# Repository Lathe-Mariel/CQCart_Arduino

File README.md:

# CQCart_Arduino
CQCart Arduino

# Overview
CQ出版から発売されているインバータ・キット2に搭載されているNUCLEOボードを，Arduino Uno R4に換装するための変換基板データを置いてあります．  
KiCADのプロジェクトになっているので，独自に改造して使用することもできます．  
This PCB board was made as a conversion board for Inverter Kit2 that is selling by CQ pub. Using this board, you can attach Arduino Uno R4 as an alternative to NUCLEO.  
 There's Garber data made by KiCAD.

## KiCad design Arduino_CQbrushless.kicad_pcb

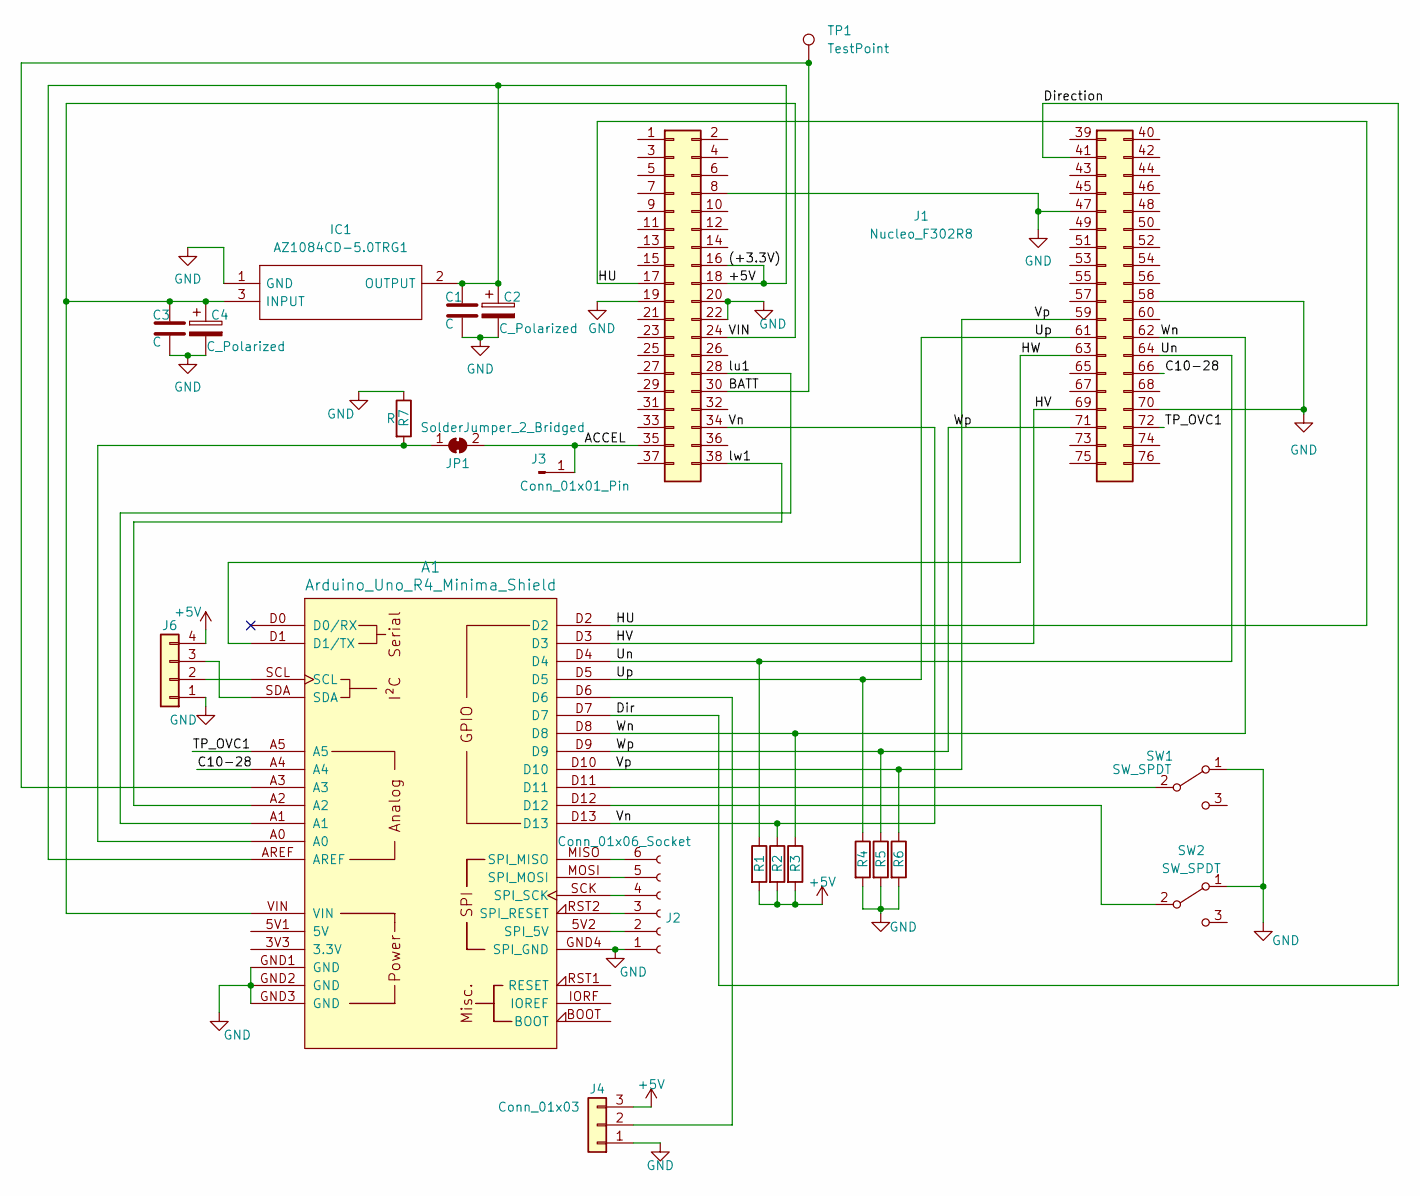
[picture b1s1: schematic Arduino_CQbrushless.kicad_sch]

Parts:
A1: Arduino_Uno_R4_Minima_Shield
C1: C; C_0805_2012Metric_Pad1.18x1.45mm_HandSolder
C2, C4: C_Polarized; CP_Radial_D8.0mm_P3.50mm
C3: C; C_0603_1608Metric_Pad1.08x0.95mm_HandSolder
IC1: AZ1084CD-5.0TRG1; AZ1084CD50TRG1; Manufacturer_Part_Number AZ1084CD-5.0TRG1
J1: Nucleo_F302R8; Nucleo
J2: Conn_01x06_Socket; PinHeader_1x06_P2.54mm_Vertical
J3: Conn_01x01_Pin; PinHeader_1x01_P2.54mm_Vertical
J4: Conn_01x03; PinSocket_1x03_P2.54mm_Vertical
J6: Conn_01x04; PinHeader_1x04_P2.54mm_Vertical
JP1: SolderJumper_2_Bridged; SolderJumper-2_P1.3mm_Bridged_Pad1.0x1.5mm
R1, R2, R3, R4, R5, R6: R; R_Axial_DIN0309_L9.0mm_D3.2mm_P12.70mm_Horizontal
R7: R; R_0603_1608Metric_Pad0.98x0.95mm_HandSolder
SW1, SW2: SW_SPDT; PinHeader_1x03_P2.54mm_Vertical
TP1: TestPoint; TestPoint_Pad_D1.5mm

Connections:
+5V: A1.AREF, C1.1, C2.1, IC1.2 (OUTPUT), J1.16, J1.18, J4.3, J6.4, R1.2, R2.2, R3.2
/ACCEL: J1.35, J3.1, JP1.2 (B)
/BATT: A1.A3, J1.30, TP1.1
/C10-28: A1.A4, J1.66
/Dir: A1.D7, J1.41
/HU: A1.D2, J1.17
/HV: A1.D3, J1.69
/HW: A1.D1 (D1/TX), J1.63
/TP_OVC1: A1.A5, J1.72
/Un: A1.D4, J1.64, R1.1
/Up: A1.D5, J1.61, R4.1
/VIN: A1.VIN, C3.1, C4.1, IC1.3 (INPUT), J1.24
/Vn: A1.D13, J1.34, R2.1
/Vp: A1.D10, J1.59, R6.1
/Wn: A1.D8, J1.62, R3.1
/Wp: A1.D9, J1.71, R5.1
/lu1: A1.A1, J1.28
/lw1: A1.A2, J1.38
GND: A1.GND1 (GND), A1.GND2 (GND), A1.GND3 (GND), A1.GND4 (SPI_GND), C1.2, C2.2, C3.2, C4.2, IC1.1 (GND), J1.8, J1.19, J1.20, J1.22, J1.47, J1.58, J1.70, J2.1, J4.1, J6.1, R4.2, R5.2, R6.2, R7.1, SW1.1 (A), SW2.1 (A)
unnamed: A1.5V2 (SPI_5V), J2.2
unnamed: A1.MISO (SPI_MISO), J2.6
unnamed: A1.MOSI (SPI_MOSI), J2.5
unnamed: A1.RST2 (SPI_RESET), J2.3
unnamed: A1.SCK (SPI_SCK), J2.4
unnamed: A1.D6, J4.2
unnamed: A1.SCL, J6.2
unnamed: A1.SDA, J6.3
unnamed: A1.A0, JP1.1 (A), R7.2
unnamed: A1.D11, SW1.2 (B)
unnamed: A1.D12, SW2.2 (B)

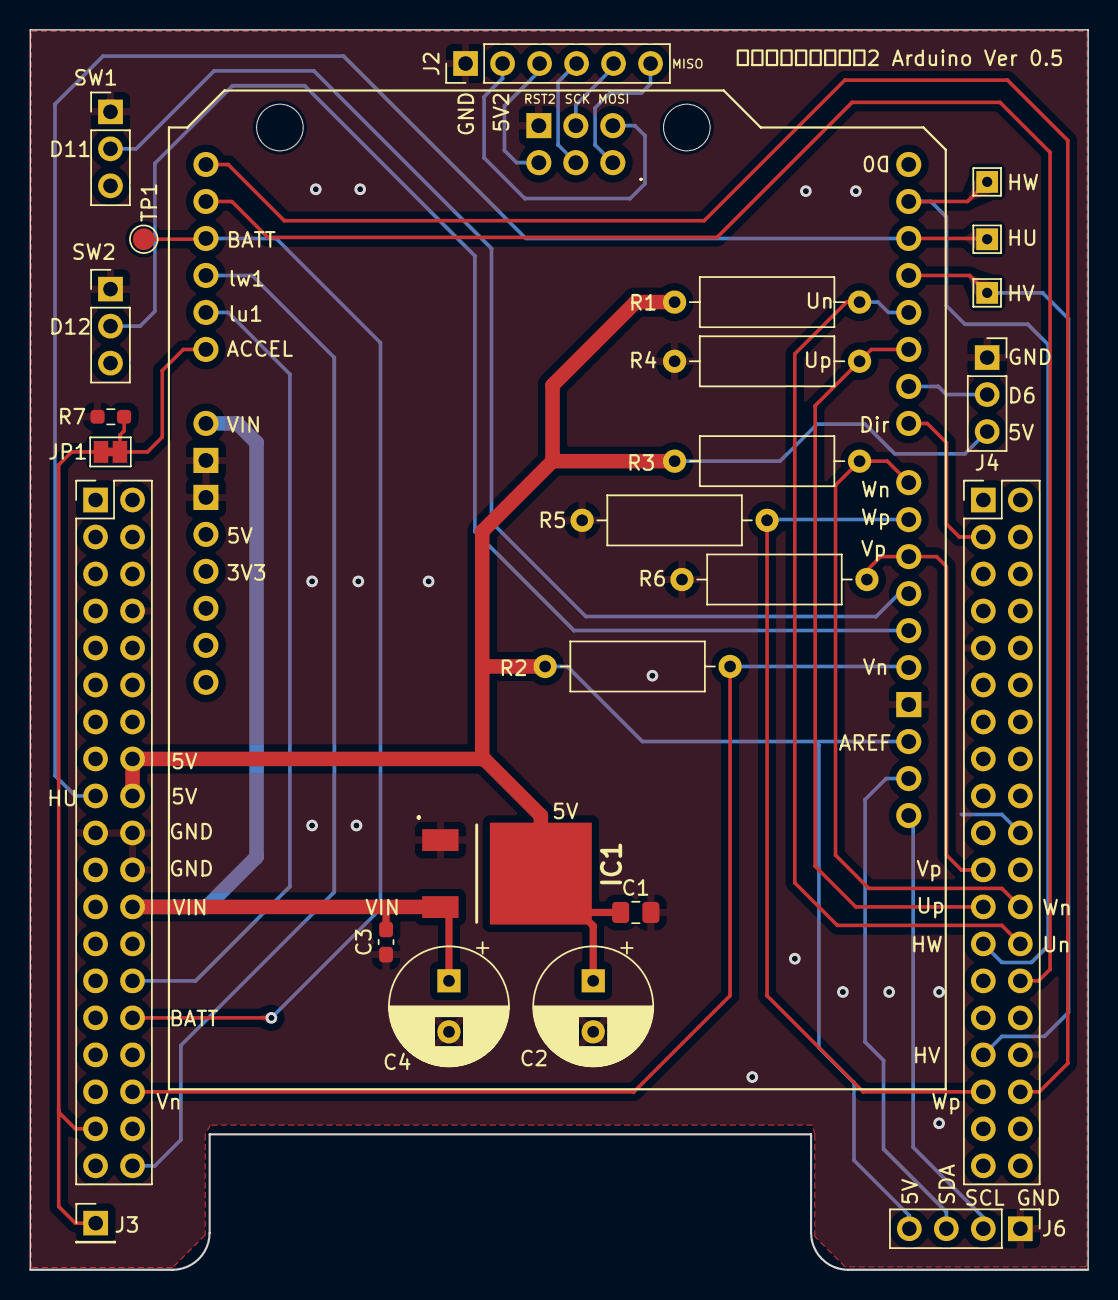
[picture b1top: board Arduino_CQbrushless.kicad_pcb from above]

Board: 2 copper layers, 72.6 x 85.1 mm, 22 parts (1 on the bottom side), 30 nets.

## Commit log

2023-12-28 1228
2024-01-08 0108
2024-01-09 0109
2024-01-18 0118
2024-01-22 0122
2024-02-07 ver0.3
2024-02-09 0209
2024-02-13 ver 0.4 (add LDO)
2024-02-14 0214
2024-02-20 0220
2024-04-16 0416
2024-05-08 0508
